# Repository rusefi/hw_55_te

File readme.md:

[rusEfi](https://github.com/rusefi/rusefi) PnP ECU for 55 pin TE 963063.

This board is a direct swap for OEM Yanvar and Mikas case. This adapter uses [microRusEFI](https://github.com/rusefi/hw_microRusEfi) as brain module.

* X injectors

* Y igniters

* 1xVR input

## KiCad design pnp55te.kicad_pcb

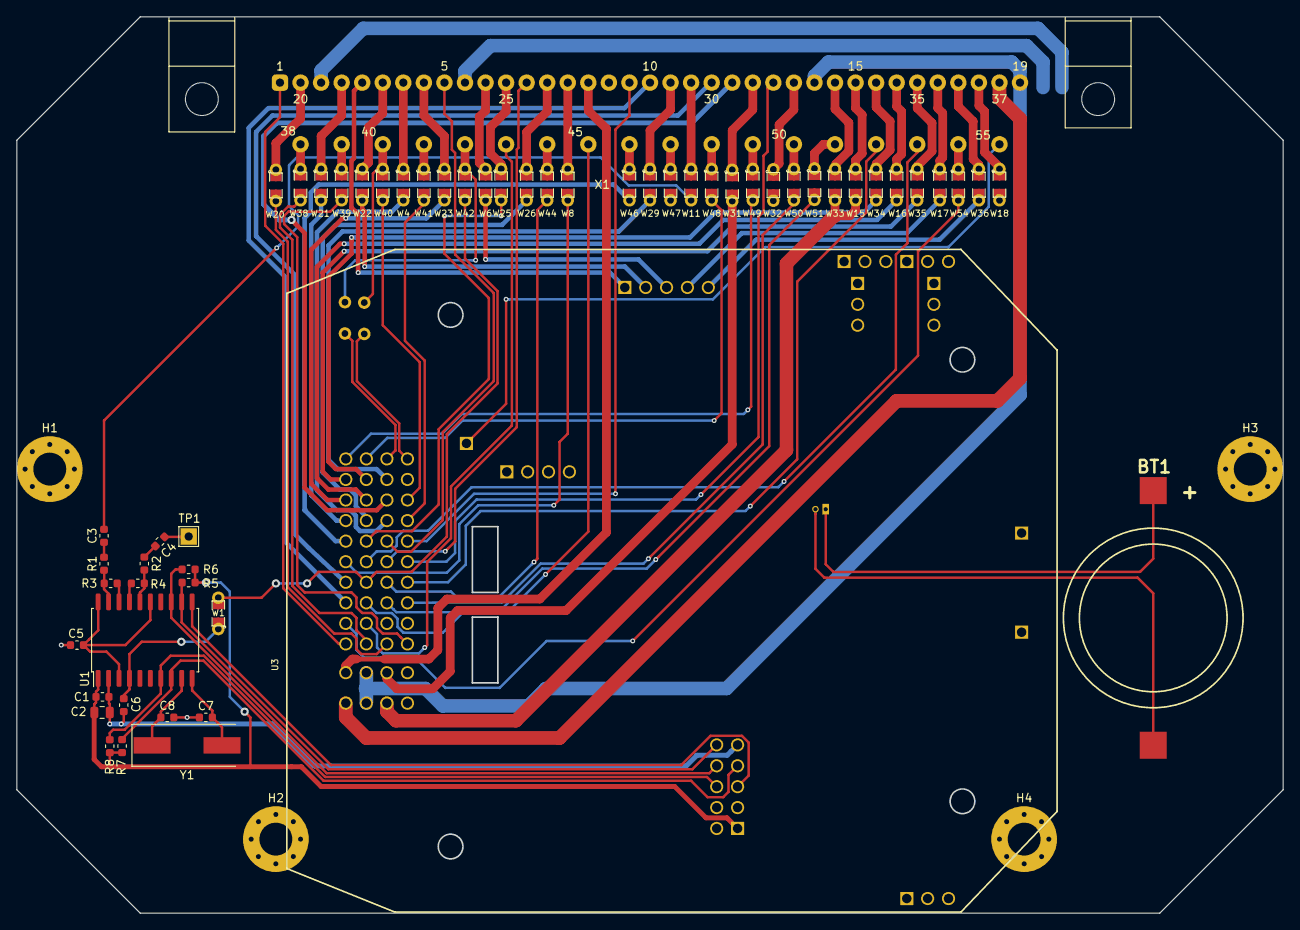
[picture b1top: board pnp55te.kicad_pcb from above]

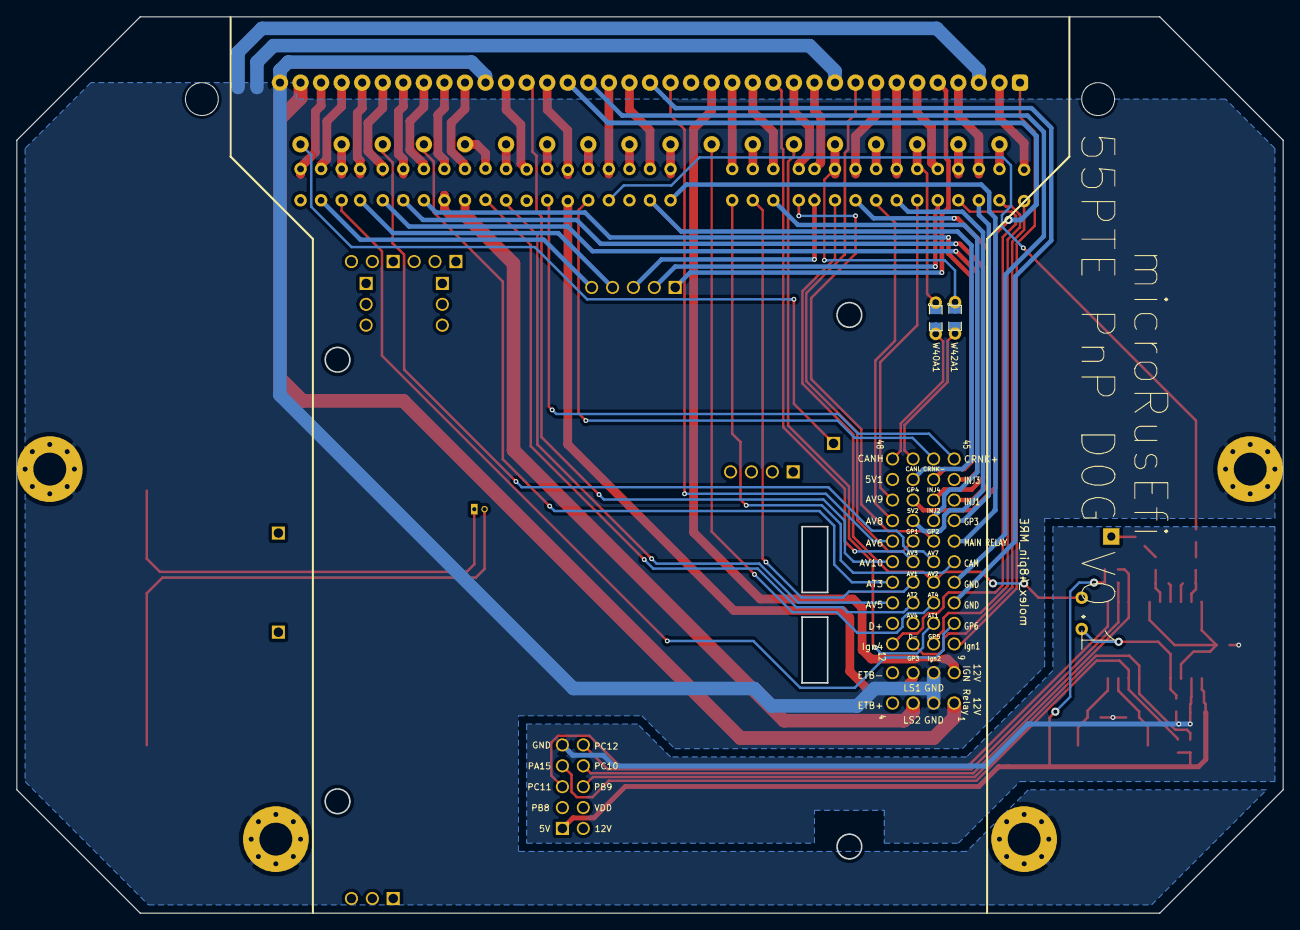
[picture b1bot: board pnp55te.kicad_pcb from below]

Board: 2 copper layers, 154.0 x 109.0 mm, 63 parts (2 on the bottom side), 103 nets.

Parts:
BT1: Battery_Cell; BATT_CR2032_MPD
C1, C5, C6: 100nF; C_0603_1608Metric
C2: 4.7uF; C_0805_2012Metric
C3, C4: 3.3nF; C_0603_1608Metric
C7, C8: 18pF; C_0603_1608Metric
H1, H2, H3, H4: MountingHole_Pad; MountingHole_4mm_Pad_Via
R1, R2, R3, R4, R5, R6, R7, R8: R; R_0603_1608Metric
TP1: TestPoint; TestPoint_THTPad_2.0x2.0mm_Drill1.0mm
U1: TPIC8101; SOIC-20W_7.5x12.8mm_P1.27mm
U3: molex_48pin_MRE; Molex_48_MRE_clean
W1: n.a. TestPoint_2Pole; SM0805_jumper
W4, W6, W8, W11, W15, W16, W17, W18, W20, W21, W22, W23, W25, W26, W29, W31, W32, W33, W34, W35, W36, W38, W39, W40, W40A1, W41, W42, W42A1, W44, W46, W47, W48, W49, W50, W51, W54: TestPoint_2Pole; SM0805_jumper
X1: 55pin_january_5.1; TE_963063-2
Y1: 8MHz; Crystal_SMD_HC49-SD

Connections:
/5V_SENS2: U3.39, X1.12
/12_IGN_KEY: U3.5, X1.27
/12_MAIN_RELAY: U3.1, X1.37
/ABSORBER_VALVE: U3.31, X1.5
/AC_RELAY: U3.30, W25.2
/AC_REQUEST: U3.36, W41.2
/AFR_HEATER: U3.3, W15.2, W33.2
/AFR_NARROW: U3.32, X1.28
/CAM_HALL: U3.25, W8.2
/CAN_H: U3.48, W40A1.2
/CAN_L: U3.47, W42A1.2
/CLT: U3.18, X1.45
/COIL1: U3.9, X1.1
/COIL2: U3.11, W20.2
/CRANK_n: U3.46, W48.2
/CRANK_p: U3.45, W49.2
/ECO_OUT: U3.13, W54.2
/EGR_POS: U3.20, W50.2
/EGR_VALVE: U3.J64, W17.2
/FAN_RELAY: U3.J63, W6.2
/FUEL_RELAY: U3.J61, X1.3
/GND_SENS_1: U3.17, X1.10
/GND_SENS_2: U3.21, X1.30
/HI2_UNUSED: U3.10, W38.2
/HI4_UNUSED: U3.12, W39.2
/IAT: U3.23, W44.2
/IDLE_STEP_A: U3.35, W4.2
/IDLE_STEP_B: U3.34, W26.2
/IDLE_STEP_C: U3.33, W21.2
/IDLE_STEP_D: U3.43, W29.2
/INJ1: U3.37, W23.2
/INJ2: U3.38, W16.2
/INJ3: U3.41, W35.2
/INJ4: U3.42, W34.2
/KNOCK_IN: C3.2, W11.2
/LIN: U3.LIN1, X1.55
/L_LINE: U3.28, X1.13
/MAF: U3.27, X1.7
/MAIN_RELAY_CONTROL: U3.29, W46.2
/MIL: U3.J62, W22.2
/MRE_5V: C1.1, C2.1, R5.1, R6.1, R7.1, R8.2, U1.1, U3.J801
/MRE_GND: C1.2, C2.2, C5.2, C6.2, C7.2, C8.2, U1.2, U3.J809
/PA15_SPI3CS: R7.2, U1.8, U3.J807
/PB9: R8.1, U1.7, U3.J806
/PC10_SPI3SCK: R6.2, U1.13, U3.J808
/PC11_SPI3MISO: U1.11, U3.J805
/PC12_SPI3MOSI: R5.2, U1.12, U3.J810
/RESERVED_AIN0: U3.40, W40.2
/RESERVED_AIN1: U3.22, W1.2, W42.2
/RESERVED_AIN2: U3.24, X1.52
/RESERVED_HI_CUR: U3.7, W31.2
/STEERING_REQ: U3.19, W51.2
/TACH: U3.14, X1.43
/TPS: U3.26, X1.53
/VAR_INTAKE: U3.J65, W36.2
/VBAT: BT1.1, U3.J31
GND: H1.1, H2.1, H3.1, H4.1, U3.2, U3.6, X1.2, X1.14, X1.19, X1.24
unnamed: BT1.2, U3.J32
unnamed: C3.1, R1.2
unnamed: C4.1, TP1.1
unnamed: C4.2, R2.2
unnamed: C5.1, U1.3, U1.15, U1.20
unnamed: C6.1, U1.4, W1.1
unnamed: C7.1, U1.10, Y1.2
unnamed: C8.1, U1.9, Y1.1
unnamed: R1.1, R3.2, U1.19
unnamed: R2.1, R4.2, U1.16
unnamed: R3.1, U1.18
unnamed: R4.1, U1.17
unnamed: W4.1, X1.4
unnamed: W6.1, X1.6
unnamed: W8.1, X1.8
unnamed: W11.1, X1.11
unnamed: W15.1, X1.15
unnamed: W16.1, X1.16
unnamed: W17.1, X1.17
unnamed: W18.1, X1.18
unnamed: W20.1, X1.20
unnamed: W21.1, X1.21
unnamed: W22.1, X1.22
unnamed: W23.1, X1.23
unnamed: W25.1, X1.25
unnamed: W26.1, X1.26
unnamed: W29.1, X1.29
unnamed: W31.1, X1.31
unnamed: W32.1, X1.32
unnamed: W33.1, X1.33
unnamed: W34.1, X1.34
unnamed: W35.1, X1.35
unnamed: W36.1, X1.36
unnamed: W38.1, X1.38
unnamed: W39.1, X1.39
unnamed: W40.1, W40A1.1, X1.40
unnamed: W41.1, X1.41
unnamed: W42.1, W42A1.1, X1.42
unnamed: W44.1, X1.44
unnamed: W46.1, X1.46
unnamed: W47.1, X1.47
unnamed: W48.1, X1.48
unnamed: W49.1, X1.49
unnamed: W50.1, X1.50
unnamed: W51.1, X1.51
unnamed: W54.1, X1.54

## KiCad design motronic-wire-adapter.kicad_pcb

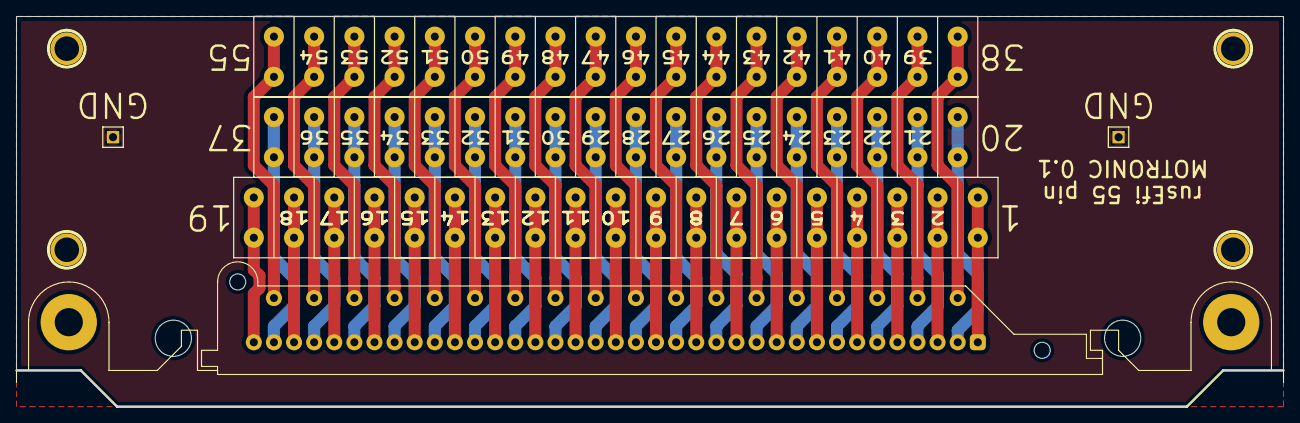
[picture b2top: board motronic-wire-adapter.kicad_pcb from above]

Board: 2 copper layers, 157.5 x 48.5 mm, 10 parts (0 on the bottom side), 56 nets.

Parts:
1PIN, 1PIN#2, 1PIN#3, 1PIN#4: P***; 1pin
P1: MOTRONIC; 55pin_china_bosch_motronic
P2: CONN_19; CON19X5
P3, P4: CONN_18; CON18X5
P5, P6: CONN_1; PIN_ARRAY_1

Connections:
GND: P5.1, P6.1
unnamed: P1.11, P2.11
unnamed: P1.1, P2.1
unnamed: P1.2, P2.2
unnamed: P1.3, P2.3
unnamed: P1.4, P2.4
unnamed: P1.5, P2.5
unnamed: P1.6, P2.6
unnamed: P1.7, P2.7
unnamed: P1.8, P2.8
unnamed: P1.9, P2.9
unnamed: P1.10, P2.10
unnamed: P1.55, P4.18
unnamed: P1.12, P2.12
unnamed: P1.13, P2.13
unnamed: P1.14, P2.14
unnamed: P1.15, P2.15
unnamed: P1.16, P2.16
unnamed: P1.17, P2.17
unnamed: P1.18, P2.18
unnamed: P1.19, P2.19
unnamed: P1.20, P3.1
unnamed: P1.21, P3.2
unnamed: P1.44, P4.7
unnamed: P1.34, P3.15
unnamed: P1.35, P3.16
unnamed: P1.36, P3.17
unnamed: P1.37, P3.18
unnamed: P1.38, P4.1
unnamed: P1.39, P4.2
unnamed: P1.40, P4.3
unnamed: P1.41, P4.4
unnamed: P1.42, P4.5
unnamed: P1.43, P4.6
unnamed: P1.22, P3.3
unnamed: P1.45, P4.8
unnamed: P1.46, P4.9
unnamed: P1.47, P4.10
unnamed: P1.48, P4.11
unnamed: P1.49, P4.12
unnamed: P1.50, P4.13
unnamed: P1.51, P4.14
unnamed: P1.52, P4.15
unnamed: P1.53, P4.16
unnamed: P1.54, P4.17
unnamed: P1.33, P3.14
unnamed: P1.23, P3.4
unnamed: P1.24, P3.5
unnamed: P1.25, P3.6
unnamed: P1.26, P3.7
unnamed: P1.27, P3.8
unnamed: P1.28, P3.9
unnamed: P1.29, P3.10
unnamed: P1.30, P3.11
unnamed: P1.31, P3.12
unnamed: P1.32, P3.13

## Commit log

2020-03-04 blank project
2020-03-04 board outline
2020-03-04 progress
2020-03-15 Add TE 55 pin connector footprint and pinout for Yanvar' 5.1
2020-03-15 Update schematic and PCB with bew symbol and footprint
2020-03-15 Do we need to track backup files?
2020-03-15 Update project file
2020-03-15 Use correct connector name
2020-03-21 fresh libraries
2020-03-21 Add fp-lib-table and sym-lib-table
2020-03-21 Use pattern from kicad-libraries
2020-03-21 Add MOTRONIC to wire adapter PCB
2020-03-21 Update gitignore
2020-04-03 Update kicad-libraries
2020-04-03 PNP adapter V0.1
2020-04-03 we do not need this
2020-04-03 image
2020-04-03 Add schwmatic in pdf format
2020-04-03 PDF new name
2020-04-03 docs
2020-04-11 Add holes for caps on bottom of MRE
2020-04-11 Add holes for caps on bottom of MRE (#5)
2020-04-21 fresh outline
2020-04-21 info
2020-04-25 fixed missing libs, misc changes.
2020-04-25 Added gerbers files.
2020-04-25 removed extra file
2020-04-25 updated JLC BOM information
2020-04-25 More BOM updates
2020-04-25 updated TPIC8108 knock chip resistors and caps.
2020-04-27 Updated GND flood
2020-04-27 Updated MRE footprint.
2020-04-28 DRAFT
2020-08-16 # this file is related to https://github.com/rusefi/kicad-libraries/blob/master/generate_diffs.sh
2020-08-16 Sorry, revert these changes
    I do not want ONE-BIG-SINGLE ground plane. Sorry.
2020-08-16 Oscilator for knock sensor, route knock sensor out to AIN, misc fixes
